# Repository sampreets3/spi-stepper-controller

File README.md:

# spi-stepper-controller
Design for an SPI based bipolar stepper motor controller, useful in robotic/3D printing applications. Makes use of the MCP23S08 SPI based I/O expander. Ideal for applications where number of GPIO is constrained. Provided with accompanying library to interface with the board.

---

## Considerations

- The design uses L293D dual H-bridge motor drivers, hence the peak current is maxed out at 1.5 A. Will not be able to drive larger stepper motors which have a higher current requirement.
- Maximum input voltage for the AMS1117-5.0 LDO chip is 15V. For best results, use ~12V supply.
- If you are working with unipolar stepper motors, change the MOTOR1 and MOTOR2 connectors to 5 pin and leave the common terminal unconnected.

---

## Schematic and Renderings

### Schematic
<details>
  <summary>Click to view the full schematic</summary>

</details>

### Layout
<details>
  <summary>Click to view the board layout</summary>
<!--

-->
</details>

---

## Contribute

- Clone or fork this repo : `git clone https://github.com/sampreets3/spi-stepper-controller.git`
- Make changes to your design and create a PR for merging

---

## Contact

You can reach me at `sampreets3@gmail.com`

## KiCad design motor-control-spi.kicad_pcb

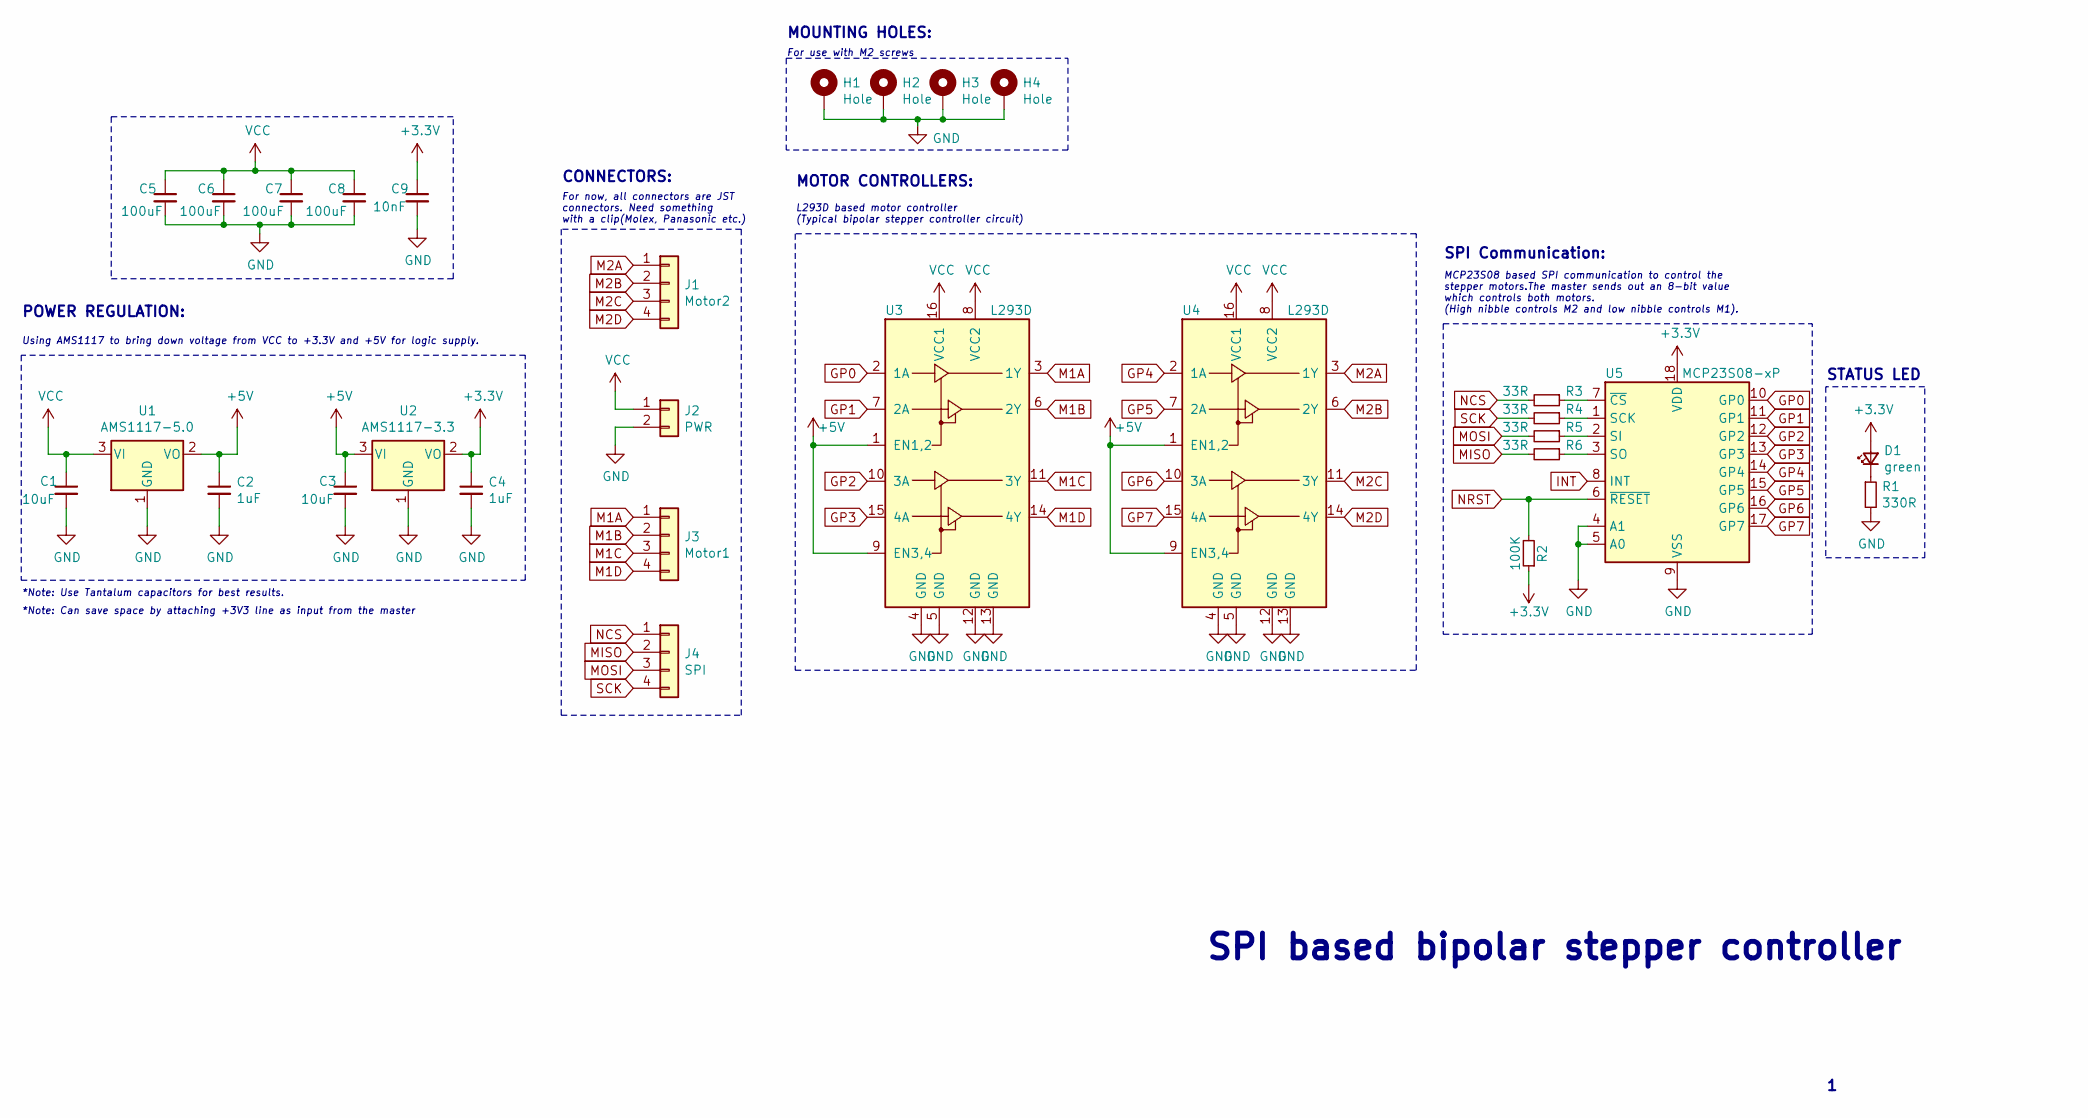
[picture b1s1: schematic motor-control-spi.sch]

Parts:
C1, C3: 10uF; C_0805_2012Metric
C2, C4: 1uF; C_0805_2012Metric
C5, C6, C7, C8: 100uF; C_0805_2012Metric
C9: 10nF; C_0805_2012Metric
D1: green; LED_1206_3216Metric_Pad1.42x1.75mm_HandSolder
H1, H2, H3, H4: Hole; MountingHole_2.2mm_M2_Pad_Via
J1: Motor2; JST_EH_S4B-EH_1x04_P2.50mm_Horizontal
J2: PWR; JST_EH_S2B-EH_1x02_P2.50mm_Horizontal
J3: Motor1; JST_EH_S4B-EH_1x04_P2.50mm_Horizontal
J4: SPI; JST_EH_S4B-EH_1x04_P2.50mm_Horizontal
R1: 330R; R_0805_2012Metric
R2: 100K; R_0805_2012Metric
R3, R4, R5, R6: 33R; R_0805_2012Metric
U1: AMS1117-5.0; SOT-223-3_TabPin2
U2: AMS1117-3.3; SOT-223-3_TabPin2
U3, U4: L293D; DIP-16_W7.62mm
U5: MCP23S08-xP; DIP-18_W7.62mm

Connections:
+3V3: C4.1, C9.1, D1.2 (A), R2.1, U2.2 (VO), U5.18 (VDD)
+5V: C2.1, C3.1, U1.2 (VO), U2.3 (VI), U3.1 (EN1,2), U3.9 (EN3,4), U4.1 (EN1,2), U4.9 (EN3,4)
GND: C1.2, C2.2, C3.2, C4.2, C5.2, C6.2, C7.2, C8.2, C9.2, H1.1, H2.1, H3.1, H4.1, J2.2, R1.2, U1.1 (GND), U2.1 (GND), U3.4 (GND), U3.5 (GND), U3.12 (GND), U3.13 (GND), U4.4 (GND), U4.5 (GND), U4.12 (GND), U4.13 (GND), U5.4 (A1), U5.5 (A0), U5.9 (VSS)
GP0: U3.2 (1A), U5.10 (GP0)
GP1: U3.7 (2A), U5.11 (GP1)
GP2: U3.10 (3A), U5.12 (GP2)
GP3: U3.15 (4A), U5.13 (GP3)
GP4: U4.2 (1A), U5.14 (GP4)
GP5: U4.7 (2A), U5.15 (GP5)
GP6: U4.10 (3A), U5.16 (GP6)
GP7: U4.15 (4A), U5.17 (GP7)
INT: U5.8 (INT)
M1A: J3.1, U3.3 (1Y)
M1B: J3.2, U3.6 (2Y)
M1C: J3.3, U3.11 (3Y)
M1D: J3.4, U3.14 (4Y)
M2A: J1.1, U4.3 (1Y)
M2B: J1.2, U4.6 (2Y)
M2C: J1.3, U4.11 (3Y)
M2D: J1.4, U4.14 (4Y)
MISO: J4.2, R6.2
MOSI: J4.3, R5.2
NCS: J4.1, R3.2
NRST: R2.2, U5.6 (~RESET)
unnamed: D1.1 (K), R1.1
unnamed: R3.1, U5.7 (~CS)
unnamed: R4.1, U5.1 (SCK)
unnamed: R5.1, U5.2 (SI)
unnamed: R6.1, U5.3 (SO)
SCK: J4.4, R4.2
VCC: C1.1, C5.1, C6.1, C7.1, C8.1, J2.1, U1.3 (VI), U3.8 (VCC2), U3.16 (VCC1), U4.8 (VCC2), U4.16 (VCC1)

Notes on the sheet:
MOUNTING HOLES:
For use with M2 screws
POWER REGULATION:
Using AMS1117 to bring down voltage from VCC to +3.3V and +5V for logic supply.
*Note: Use Tantalum capacitors for best results.
*Note: Can save space by attaching +3V3 line as input from the master
CONNECTORS:
For now, all connectors are JST connectors. Need something with a clip(Molex, Panasonic etc.)
MOTOR CONTROLLERS:
L293D based motor controller (Typical bipolar stepper controller circuit)
SPI Communication:
MCP23S08 based SPI communication to control the stepper motors.The master sends out an 8-bit value which controls both motors. (High nibble controls M2 and low nibble controls M1).
STATUS LED
SPI based bipolar stepper controller

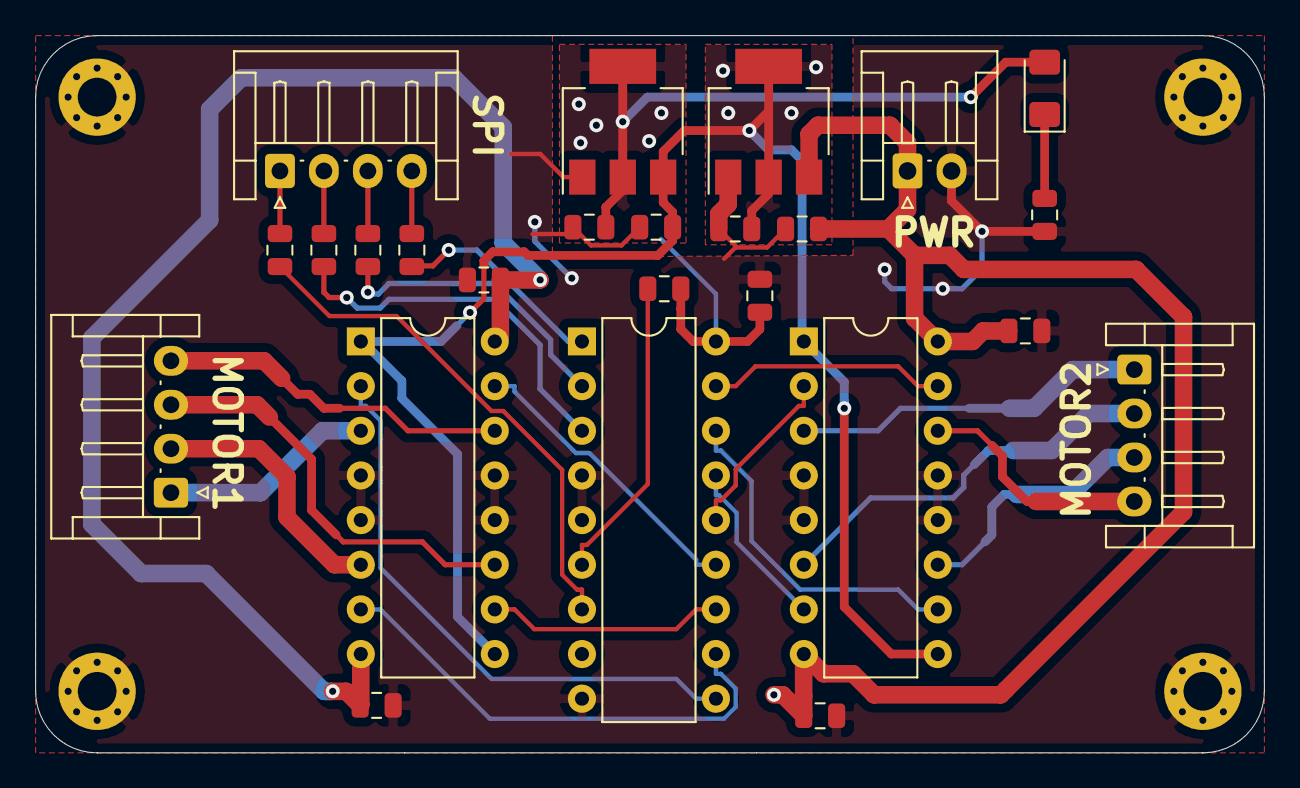
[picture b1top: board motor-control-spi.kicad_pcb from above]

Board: 2 copper layers, 69.9 x 40.8 mm, 29 parts (0 on the bottom side), 30 nets.

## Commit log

2020-08-25 Added support libraries
2020-08-25 Added images and schematics to README

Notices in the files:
README.md:
GPLv3 license
